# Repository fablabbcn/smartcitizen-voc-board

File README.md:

# Smart Citizen VOC Board

This board is a small experimental board for interfacing Figaro [TGS2600](https://figarosensor.com/product/entry/tgs2600.html) and [TGS2602](https://figarosensor.com/product/entry/tgs2602.html) with the [Smart Citizen Analog Sensor Board](https://github.com/fablabbcn/smartcitizen-analog-sensor-board).

## BOM

### For the board

- 1x Figaro TGS2600
- 1x Figaro TGS2602
- 2x 1206 Resistors (we use 1kOhm)
- 1x 5-pin male header with polarity ([here](https://www.mouser.es/ProductDetail/Molex/22-23-2051?qs=ILqg114nvd59B%2FNFe4wunQ%3D%3D) in mouser)

### For the cable

- 5x pre-crimped cables 150mm ([here](https://www.mouser.es/ProductDetail/Molex/79758-0007?qs=%2Fha2pyFadugCSZI%2Fv6p%252BNwepMMZmmpAOQPZNkNseSc9YFWZHmU8YCQ%3D%3D)) in mouser
- 2x 5-pin header ([here](https://www.mouser.es/ProductDetail/Molex/22-01-3057?qs=dvxwXVM4mZX5H9Q4idh0EQ%3D%3D) in mouser)

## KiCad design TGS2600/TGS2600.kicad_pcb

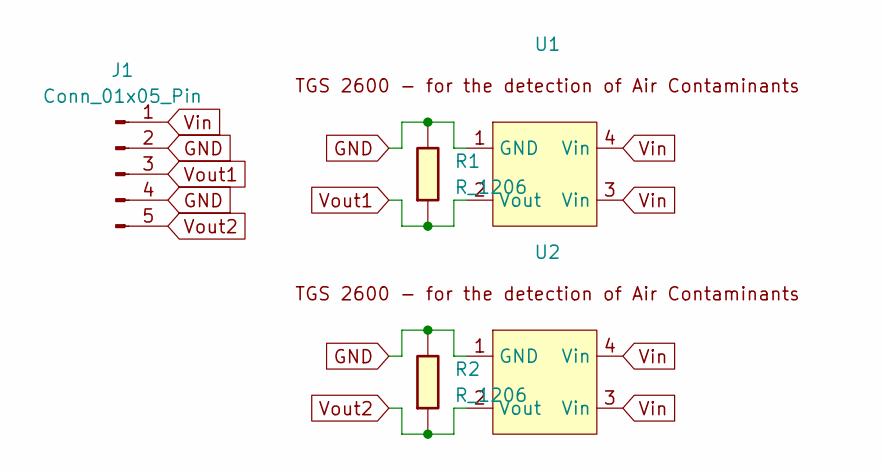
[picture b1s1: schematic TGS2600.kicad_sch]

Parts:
J1: Conn_01x05_Pin; PinHeader_1x05_P2.54mm_Vertical
R1, R2: R_1206; R_1206_3216Metric
U1, U2: TGS-2600

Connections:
GND: J1.2, J1.4, R1.1, R2.1, U1.1 (GND), U2.1 (GND)
Vin: J1.1, U1.3 (Vin), U1.4 (Vin), U2.3 (Vin), U2.4 (Vin)
Vout1: J1.3, R1.2, U1.2 (Vout)
Vout2: J1.5, R2.2, U2.2 (Vout)

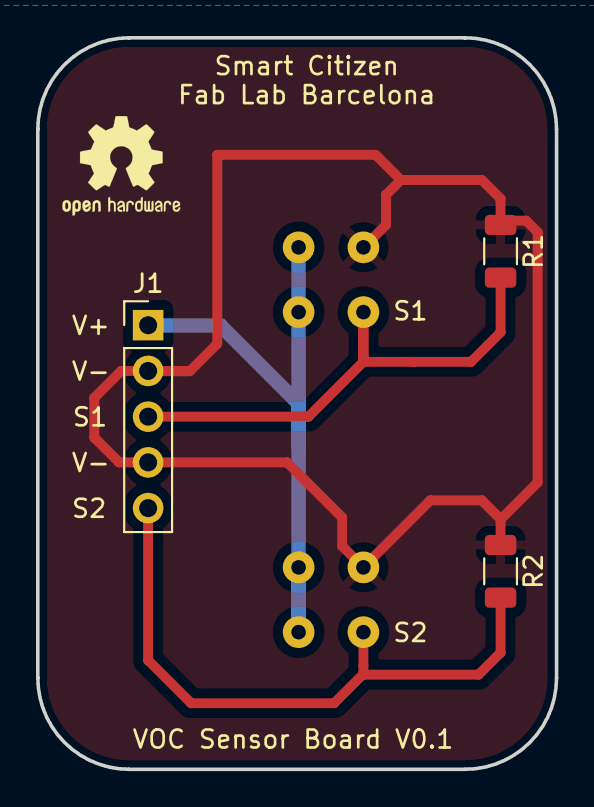
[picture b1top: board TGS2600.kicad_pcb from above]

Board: 2 copper layers, 28.8 x 40.6 mm, 5 parts (0 on the bottom side), 4 nets.

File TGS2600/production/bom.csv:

Designator,Footprint,Quantity,Value,LCSC Part #
J1,PinHeader_1x05_P2.54mm_Vertical,1,Conn_01x05_Pin,
"R1, R2",1206,2,R_1206,
"U1, U2",TGS-2600,2,~,

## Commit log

2024-08-08 TGS2600 TGS2602
2024-08-08 empty README.md
2024-09-05 Update for manufacturing
2024-09-05 Fabrication exports for jlcbpcb
2024-09-06 Fix mounting holes preventing manufacturing
